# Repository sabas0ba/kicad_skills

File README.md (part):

#  kicad_skills — a containerised circuit-design toolkit

`eda` is a command-line toolkit for circuit design work: reading datasheets,
simulating analog circuits with ngspice, reviewing KiCad schematics and PCB
artwork, and producing the fabrication package.

**Everything runs inside a container.** KiCad, ngspice and the Python
dependencies are never installed on the host — the only host requirements are
`docker` and `bash`. The KiCad release is a build argument, so it can be pinned
per project.

It is an ordinary CLI that prints JSON and exits non-zero on errors, so it works
the same from a terminal, a `Makefile`, a CI job, or a coding assistant. The
repository also ships [usage guides](docs/guides/README.md) for each area —
plain Markdown, worth reading on their own, and installable into whatever layout
your assistant expects.

```bash
./bin/eda.sh doctor                                   # builds the image on first use
./bin/eda.sh gate        hardware/ --policy ai-generated --text   # pass or fail, and why
./bin/eda.sh report      hardware/ -o build/report    # everything, on one page
./bin/eda.sh sch review  hardware/ --text
./bin/eda.sh pcb review  hardware/ --text
./bin/eda.sh sim run     sim/filter.cir -o sim/out
./bin/eda.sh datasheet parse docs/datasheets/lm321.pdf -o /tmp/ds
```

## Install

### Into an existing board project, as a submodule

```bash
cd ~/projects/my-board
git submodule add https://github.com/sabas0ba/kicad_skills tools/kicad_skills
./tools/kicad_skills/bin/install-skills.sh
```

That drops a one-line `bin/eda.sh` shim so the `./bin/eda.sh …` commands work
verbatim from your project root and links the [usage guides](docs/guides/README.md)
into the standard layouts discovered by Codex, compatible assistants, and
Claude Code:

```
my-board/
├── bin/eda.sh                                    shim -> tools/kicad_skills/bin/eda.sh
├── .agents/skills/kicad-pcb-review/SKILL.md ->   ../../../tools/kicad_skills/docs/guides/kicad-pcb-review.md
├── .claude/skills/kicad-pcb-review/SKILL.md ->   ../../../tools/kicad_skills/docs/guides/kicad-pcb-review.md
├── hardware/my-board.kicad_pro
└── tools/kicad_skills/                           the submodule
```

Commit `bin/eda.sh` so everyone who clones the project gets it. Upgrading is
`git submodule update --remote` — the symlinks follow, with no re-install.
The generated skill layouts are outside the submodule, so add `.agents/skills/`
and `.claude/skills/` to the parent project's `.gitignore` unless the project
chooses to track those adapters.

| Flag | Effect |
| --- | --- |
| `--no-guides` | just the CLI shim, nothing else |
| `--dest DIR` | another tool's directory (e.g. `--dest .cursor/rules`) |
| `--copy` | vendor the guides instead of symlinking (Windows checkouts) |
| `--force` / `--uninstall` | replace what is already there / reverse the install |

The guides themselves need no install — they are Markdown in
`tools/kicad_skills/docs/guides/`, readable as they are.

Then, from your project root:

```bash
./bin/eda.sh doctor                       # builds the image on first use (~5 min)
./bin/eda.sh report hardware/ -o build/report
```

### Or standalone

No install step is needed to try it — clone and run:

```bash
git clone https://github.com/sabas0ba/kicad_skills && cd kicad_skills
./bin/eda.sh doctor            # {"kicad_cli": "10.0.4", "ngspice": "...", "ok": true}
./bin/eda.sh report ~/projects/my-board/hardware -o /tmp/report
```

`bin/eda.sh` mounts the git repository root that contains the current directory
at `/work`, runs as your uid/gid (no root-owned files), and gives the container
no network. To work on the toolkit itself, see [AGENTS.md](AGENTS.md).

If you drive this clone with Codex, another Agent Skills-compatible assistant,
or Claude Code, `make skills` mirrors the guides into the layouts they discover.
Those directories are generated and git-ignored — the guides live in
[`docs/guides/`](docs/guides/README.md).

## What it does

```mermaid
flowchart LR
    PDF[datasheet PDF] --> DS[eda datasheet]
    DS -->|part values| SIM[eda sim]
    SIM -->|verified circuit| SCH[eda sch review]
    SCH -->|netlist + ERC| PCB[eda pcb review]
    SCH --> GATE[eda gate]
    PCB --> GATE
    GATE -->|pass| FAB[eda pcb fab]
    SCH --> REP[eda report]
    PCB --> REP
    SIM --> REP
    REP --> HTML[report.html + PNG + PDF + GLB]
```

| Area | What it does | One command | Guide |
| --- | --- | --- | --- |
| Datasheets | Text, parameter tables, embedded figures and rendered page images from a PDF | `eda datasheet parse lm321.pdf -o out/` | [guide](docs/guides/datasheet-analysis.md) |
| Simulation | ngspice op/dc/ac/tran/noise, THD, Monte Carlo tolerance analysis, temperature sweeps — with measurements and plots | `eda sim run filter.cir -o out/` | [guide](docs/guides/spice-simulation.md) |
| Schematic review | Components, nets and hierarchy from `.kicad_sch`; ERC plus decoupling / floating-input / annotation / pull-up checks, drawing readability (grid, junctions, overlap, page) and part specification (ratings, derating, part numbers) | `eda sch review hardware/ --text` | [guide](docs/guides/kicad-schematic-review.md) |
| Board review | DRC, schematic parity, track widths, drills, exact board-edge clearance, ground pour, silkscreen over pads, placement grid and rotation, track stubs and acute corners, decoupling vias; current capacity, resistance and impedance from the stackup — closed forms, or a 2D field solve with `--solve`; a steady-state temperature map and heating curve for stated dissipations (`pcb thermal`); near- and far-end crosstalk of the coupled runs from solved line matrices (`pcb crosstalk`); layer plots and 3D renders | `eda pcb review hardware/ --text` | [guide](docs/guides/kicad-pcb-review.md) |
| Design gate | One pass/fail verdict over ERC, DRC and both reviews against a stated policy; readability, layout-practice and part-specification rules; waivers that must carry a reason | `eda gate hardware/ --policy ai-generated` | [guide](docs/guides/kicad-design-gate.md) |
| Fabrication | Gerbers, Excellon drill, pick-and-place, BOM, STEP/IPC-2581, zipped with a manifest | `eda pcb fab hardware/ -o fab/` | [guide](docs/guides/kicad-fabrication-output.md) |
| The container | Build, pin, verify and troubleshoot the toolchain | `eda doctor` | [guide](docs/guides/eda-environment.md) |

### Examples

**Review a board and see why** — findings are structured, so they can be
filtered, counted and gated on in CI; `--text` is the human digest.

```console
$ ./bin/eda.sh pcb review hardware/ --text
## summary: error=1, warning=3, info=4

## findings
  ERROR   board.copper_outside_outline: 46 copper item(s) lie outside the board outline
  WARNING board.edge_clearance: 2 copper item(s) within 0.3 mm of the board outline
  WARNING layout.decoupling_distance [U3.14 / +3V3]: C12 is 8.4 mm away
  INFO    board.size: board outline is 63.5 x 40.6 mm
```

Exit code is `2` when a review found errors, so `eda pcb review hardware/` is
also a CI gate; `-o report.json` keeps the structured version.

**Hold a generated design to a standard** — a review lists what is wrong; a
gate says whether that is acceptable, against a policy the project committed to.

```console
$ ./bin/eda.sh gate hardware/ --policy ai-generated --text
# gate FAIL: hardware/ against policy 'ai-generated'

## after the policy: error=11, warning=0, info=2
  over the limit: 11 error(s), 0 allowed

## blocking
  ERROR   schematic/readability.off_grid_pin: 12 pin(s) are off the 1.27 mm grid -
          wires that meet them look connected and are not (reported as warning)
  ERROR   schematic/spec.voltage_derating [/:C7]: C7 is rated 6.3 V and sits on a 12 V rail
  ERROR   board/silk.over_pad: 4 silkscreen item(s) print across a pad (reported as warning)

## waived
  drc.lib_footprint_mismatch: our footprints are project-local copies
```

None of that is something ERC or DRC has an opinion about, which is exactly why
a design can be ERC-clean, DRC-clean and still be one no engineer would sign.
`(reported as warning)` is the policy at work — and a waiver without a stated
reason is refused, so nothing is passed over quietly.

`eda gate --list-rules` prints the whole contract: every rule, the exact
condition that makes it fire, the threshold that tunes it and its default, and
the policies under which it blocks. It is assembled from the rule modules, and
`tests/test_rule_spec.py` reads their source, so a rule the catalogue does not
describe — or an entry no rule produces — fails the build. See the
[design gate guide](docs/guides/kicad-design-gate.md) for the evaluation rules
and the exit codes.

**Simulate before committing to a part value** — the −3 dB corner, the phase
margin and the tolerance spread come back as numbers, not a picture to squint at.

```console
$ ./bin/eda.sh sim montecarlo sim/rc.cir -o sim/mc \
    --vary R1=1% --vary C1=10% --metric 'ac.v(out).f_minus_3db_hz' --trials 200
{"metric": "ac.v(out).f_minus_3db_hz", "nominal_metric": 997.7,
 "statistics": {"samples": 200, "mean": 1001.1, "stdev": 35.5,
                "p05": 940.1, "median": 1000.7, "p95": 1064.0, "spread_pct": 20.4},
 "sensitivity": {"explained_pct": 99.7, "parameters": [
     {"parameter": "C1", "contribution_pct": 99.3, "elasticity": -0.99},
     {"parameter": "R1", "contribution_pct":  0.7, "elasticity": -0.96}]},
 "failures": [], "histogram": "sim/mc/histogram.png", "csv": "sim/mc/trials.csv"}
```

The 10 % capacitor is the entire spread; the 1 % resistor is noise. That is the
line item worth changing, and it came out of the trials that were already run.

**Read a datasheet without opening a viewer** — page images for the curves,
tables for the numbers.

```console
$ ./bin/eda.sh datasheet find docs/lm321.pdf "supply current"
[{"page": 3, "line": "Supply Current  IS  VS = 5 V, no load  0.43  0.75  mA"}]
$ ./bin/eda.sh datasheet pages docs/lm321.pdf -o out/ --pages 7 --dpi 200
```

**One command for the whole project** — see [the worked example](#worked-example-a-real-board)
below.

```bash
./bin/eda.sh report hardware/ -o build/report --glb
open build/report/report.html
```

## What the gate is worth, in pictures

Five complete designs are generated by [`tools/make_examples.py`](https://github.com/sabas0ba/kicad_skills/blob/main/tools/make_examples.py)
and shipped twice: once as the generator first left them, and once after
`eda gate` had been run and every finding answered. Same circuit, same nets,
same parts — the difference is entirely what the gate had an opinion about.

**A schematic.** The Pico carrier. On the left: an empty title block, not one
note, and eighteen power symbols pointing in four different directions. On the
right: a title that says what the board is, fifteen notes recording why the
values are what they are, and every power symbol upright:

| as generated | after the gate |
| --- | --- |
|  |  |

**A board.** The 12 V → 5 V buck. On the left: no ground pour, not one via,
every track 0.25 mm whatever it carries, and nothing on the silkscreen at all.
On the right: the plane poured on both faces and stitched with 79 vias, power
copper at 1.0 mm and tapered into every land, screw holes that clear an M3
washer, and a regulator tab relieved so a reflow oven can still solder it:

| as generated | after the gate |
| --- | --- |
|  |  |

**And the motor driver**, which went from one track width for the whole board
to fifteen — motor outputs, logic and the charge pump each sized for what they
carry — and gained the plane its H-bridge returns through:

| as generated | after the gate |
| --- | --- |
|  |  |

The scoreboard, under each project's own policy:

| design | as generated | after the gate |
| --- | --- | --- |
| buck-5v | **FAIL** — 45 blocking | **PASS** |
| motor-driver | **FAIL** — 43 blocking | **PASS** |
| pico-carrier | **FAIL** — 50 blocking | **PASS** |
| opamp-filter | **FAIL** — 33 blocking | **PASS** |
| fpga-audio | **FAIL** — 34 blocking | **PASS** |

All five gated boards are clean under KiCad's own DRC on both versions in the
matrix, with nothing unconnected, and every finding that remains is a waiver
carrying the sentence that excuses it.

**[examples/](examples/README.md) is the long version**: all five designs, both
faces of every board, a third column showing what the generator produces *today*
(the reviews went into the generator, not into patches on its output), and
[REVIEW.md](examples/REVIEW.md) — twenty rounds of a reviewer reading the
boards, and what each finding became: a rule, a fix, or a waiver with its
argument.

## Pinning the KiCad version

```bash
KICAD_VERSION=10.0.4 make build     # default, current stable
KICAD_VERSION=9.0.9  make build     # a second image for older projects
KICAD_VERSION=9.0.9 ./bin/eda.sh pcb review board.kicad_pcb
```

Each version produces its own image tag (`eda-toolkit:<version>`) so several can
coexist. Tags: <https://hub.docker.com/r/kicad/kicad/tags>. KiCad upgrades
project files in place when it opens something older than itself, so match the
version to the project.

CI runs the **whole suite against both 10.0.4 and 9.0.9**, because "the KiCad
version is configurable" is a claim that has to be backed up. It is what caught
these, all of which are handled at runtime rather than pinned away:

* `pcb export pdf --scale`, `pcb export gerbers --check-zones`,
  `pcb drc --refill-zones` and `pcb export stats` are KiCad 10 additions. The
  wrapper asks the binary what it supports (`kicad_cli.supports`) instead of
  keeping a version table, so an untested release degrades rather than crashes.
* ngspice never initialises the imaginary half of an AC sweep's frequency
  column. ngspice 44 leaves a denormal there and taking the magnitude looks
  fine; the ngspice 39 that ships with KiCad 9 left `-1.8e199`, and every
  frequency measurement became nonsense. Only the real part is defined.

Adding a version is a digest in `docker/kicad-digests.txt` plus an entry in the
workflow matrix — `tests/test_pinning.py` fails if the two disagree.

## Worked example: a real board

Everything below is actual output from the **Open Air Max** demo project that
ships with KiCad (210 footprints, 4 layers, a 3-sheet hierarchical schematic) —
a far better test of "does this help?" than a two-resistor fixture. One command
produced all of it:

```bash
./bin/eda.sh report openair-max/ -o build/report --dpi 150 --glb
```

```
build/report/
├── report.html          the page below, self-contained
├── report.md            same content, for a PR comment or a commit message
├── report.json          every finding, machine readable
├── bom.csv
├── schematic/           schematic.pdf + one PNG per sheet + contact sheet
└── board/               6 view plots, 4 per-layer plots, 3 renders,
                         contact-sheet.png, board.glb, the PDFs behind them
```

**The board at a glance** — 13 plots and renders tiled into one image, so
"is anything on the wrong layer" is one look, not thirteen file-opens:

**3D, for the things no 2D plot shows** — connector orientation, component
collisions, which side is which. `--glb` additionally writes a `board.glb` that
GitHub and every browser render interactively:

**The schematic**, rasterised per sheet plus a real PDF (sheet 1 of 3):

**And the verdict**, abridged from `report.md` — note the collapsing: 199
identical drill violations are one line, not 199:

```markdown
## Verdict
* schematic: 3 error, 19 warning, 4 info
* board: 8 error, 26 warning, 6 info
* 99.45 x 72.0 mm, 4 layers, 210 footprints, 156 nets, 410 vias

## Board findings
| severity | rule | where | message |
| --- | --- | --- | --- |
| error   | `drc.drill_out_of_range` | 199 locations | 199 occurrences. First: Hole size out of range (min hole 0.5080 mm; actual 0.4000 mm) |
| error   | `drc.clearance`          | 13 locations  | 13 occurrences. First: Clearance violation (clearance 0.1000 mm; actual 0.0910 mm) |
| error   | `drc.zones_intersect`    | Zone [BAT-] on F.Cu, priority 5 | Copper zones intersect (must have distinct priorities) |
| warning | `drc.parity.net_conflict`| Pad 6 of I2C3 on B.Cu | Pad net doesn't match net given by schematic (GND) |
| warning | `drc.silk_edge_clearance`| 8 locations   | 8 occurrences. First: Silkscreen clipped by board edge |
```

### Simulation

The same "show, don't describe" applies to analog work. An AC sweep of the RC
reference circuit, and 200 Monte Carlo trials of the same circuit with 1 %
resistors and 10 % capacitors:

| `sim run` (AC) | `sim montecarlo` |
| --- | --- |
|  |  |

```json
{"nominal_metric": 997.7,
 "statistics": {"samples": 200, "mean": 1001.1, "stdev": 35.5,
                "p05": 940.1, "median": 1000.7, "p95": 1064.0, "spread_pct": 20.4}}
```

The 10 % capacitor sets the spread: ±1 % on the resistor barely moves it. That
is the kind of answer that changes a BOM line.

Provenance and licensing of these images: [`docs/examples/README.md`](docs/examples/README.md).

## Command reference

```
eda doctor                                    tool versions in the environment
eda gate         TARGET [--policy NAME|FILE] [--text] [--threshold KEY=VALUE]
                        [--collapse N] [-o verdict.json]
eda gate         --list-policies | --list-rules [--text]
eda diff         OLD NEW -o DIR [--dpi 150] [--no-images]
eda report       TARGET -o DIR [--dpi 200] [--glb] [--simulation NETLIST]
                              [--no-3d] [--no-per-layer] [--no-bom] [--title T]

eda datasheet info   PDF
eda datasheet find   PDF QUERY... [--regex]
eda datasheet text   PDF [--pages 1-5] [--layout] [--ocr]
eda datasheet tables PDF [--pages 5]
eda datasheet images PDF -o DIR [--pages]
eda datasheet pages  PDF -o DIR [--pages] [--dpi 200]
eda datasheet parse  PDF -o DIR [--renders] [--ocr]

eda sim lint     NETLIST
eda sim run      NETLIST -o DIR [--no-plots] [--timeout S]
eda sim montecarlo NETLIST -o DIR --vary R1=1% --metric ac.v(out).f_minus_3db_hz [--trials N]
eda sim temperature NETLIST -o DIR [--temperatures -40 25 85] [--metric ...]
eda sim measure  RAW [--thd SIGNAL --fundamental HZ] [--skip S]
eda sim plot     RAW -o DIR [--signals ...]
eda sim netlist  SCHEMATIC -o FILE           export a SPICE deck from KiCad

eda sch info     TARGET [--no-cli]
eda sch review   TARGET [--text] [--collapse N] [--threshold KEY=VALUE] [-o report.json] [--no-cli]
eda sch bom      TARGET -o bom.csv [--group-by ...] [--fields ...]
eda sch erc      TARGET                      raw KiCad ERC JSON
eda sch netlist  TARGET [--format json|kicadxml|spice|...] [-o FILE]
eda sch render   TARGET -o DIR [--dpi 200]   PDF + one PNG per sheet + contact sheet
eda sch pdf      TARGET -o FILE              just the PDF

eda pcb info     TARGET
eda pcb review   TARGET [--text] [--collapse N] [--threshold KEY=VALUE] [-o report.json]
eda pcb fab      TARGET -o DIR [--step] [--ipc2581] [--pos-format csv]
                              [--preview] [--background white|black|transparent]
eda pcb drc      TARGET [--no-parity]        raw KiCad DRC JSON
eda pcb render   TARGET -o DIR [--views ...] [--per-layer] [--no-3d] [--no-sheet]
                              [--glb] [--dpi 300]
                              [--background white|black|transparent]
eda pcb glb      TARGET -o FILE              3D model a browser can display
eda pcb electrical TARGET [--temperature-rise K] [--top N] [--solve]
eda pcb crosstalk TARGET [--rise-ns NS] [--swing V] [--min-coupled MM] [--limit N]
                              [-o DIR]
eda pcb thermal  TARGET --power REF=W [--power ...] [--ambient C] [--htc W_M2K]
                              [--step MM] [--transient S] [-o DIR]
eda pcb stats    TARGET
```

`TARGET` accepts a `.kicad_sch`/`.kicad_pcb` file, a `.kicad_pro`, or a project
directory. All commands print JSON by default (the review commands also take
`--text` for a human readable digest) and exit `2` when a review found errors.

### Environment variables

| Variable | Effect |
| --- | --- |
| `KICAD_VERSION` | KiCad release / image tag to use (default `10.0.4`) |
| `EDA_IMAGE` | override the image name entirely |
| `EDA_NETWORK` | `1` gives the container network access (default: offline) |
| `EDA_MOUNT` | host directory to mount at `/work` (default: git root or `$PWD`) |
| `EDA_ENV_PASSTHROUGH` | extra environment variable names to forward |
| `EDA_DOCKER_ARGS` | extra arguments for `docker run` |

## Using it in CI

The reviews are exit-code gates, so a board can be checked on every push the way
code is. In a project that added this as a submodule:

```yaml
# .github/workflows/hardware.yml
- uses: actions/checkout@... # with: submodules: true
- name: Gate the design
  run: ./bin/eda.sh gate hardware/ --policy hardware/gate.toml --text
- name: Review the board
  if: always()
  run: |
    ./bin/eda.sh sch review hardware/ --text
    ./bin/eda.sh pcb review hardware/ --text
- name: Build the report
  if: always()
  run: ./bin/eda.sh report hardware/ -o build/report
- uses: actions/upload-artifact@...
  if: always()
  with: { name: hardware-report, path: build/report }
```

On a pull request the more useful question is what changed. `eda diff` answers it
against the design rather than the file: a moved component rewrites thousands of
coordinates in the `.kicad_pcb`, and a text diff cannot tell that apart from a
rerouted net.

```yaml
- name: What changed
  run: |
    git worktree add /tmp/base "$GITHUB_BASE_REF"
    ./bin/eda.sh diff /tmp/base/hardware hardware/ -o build/diff
    cat build/diff/diff.md >> "$GITHUB_STEP_SUMMARY"
```

```markdown
## Connectivity
* **VCC**: gained U3.14, lost -
## Components
* **R7**: value '10k' -> '4k7'
## Board
* moved: U3 (5.0 mm), C12 (1.2 mm)
## Artwork
* `copper-front`: 0.28% of pixels changed
```

Both drawings are rendered and compared too — the schematic sheets and the board
plots. What only the old revision had is drawn in **red**, what only the new one
has in **green**, over a faded copy of the new drawing, so a part that moved reads
as red where it was and green where it is now. Where the change is a speck on an
A4 sheet, a zoomed crop is written alongside the full page:

| schematic: C2 moved, R1 re-valued | board: the same R1 move |
| --- | --- |
|  |  |

Exit `0` clean, `1` on a usage error, `2` when a review found errors. Loosen or
tighten what counts as an error with `--threshold KEY=VALUE`, or post-process
`report.json` if you want your own policy. This repository's own CI reviews its test
fixture and uploads the report the same way — see
[`ci.yml`](https://github.com/sabas0ba/kicad_skills/blob/main/.github/workflows/ci.yml).

Nothing needs the network at run time, so the container stays offline unless you
ask for `EDA_NETWORK=1`.

## Using it with a coding assistant

The toolkit is a CLI: any assistant that can run a shell command can drive it,
and the JSON output is meant to be parsed rather than screen-scraped. What makes
the difference in practice is not the commands but knowing how to *use* them —
which is what [`docs/guides/`](docs/guides/README.md) is for. Those guides cover
the review methodology, what each finding means, and what the tool cannot judge
for you.

* **Codex and Agent Skills-compatible assistants** discover
  `.agents/skills/<name>/SKILL.md`.
* **Claude Code** discovers `.claude/skills/<name>/SKILL.md`.
* `bin/install-skills.sh` creates both layouts as symlinks by default. Run it in
  this checkout or in a project that uses the submodule. This checkout ignores
  the generated adapters; a parent project must ignore or track its own copies.
* **A tool with another layout** — use
  `./bin/install-skills.sh --dest .cursor/rules --copy`; specifying `--dest`
  installs only that layout.
* **Anything that reads a repository** can instead read `docs/guides/` or
  [`AGENTS.md`](AGENTS.md), which names the guides.
* **No assistant at all** — they are ordinary Markdown, written to be read.

Contributor and agent instructions for this repository itself live in
[`AGENTS.md`](AGENTS.md) (`CLAUDE.md` is a pointer to it, not a second copy).

`eda gate` is the other half of that story. An assistant that generates a
design will read a page of warnings and move on unless something says which of
them were allowed to survive; the gate is that statement, and its exit code is
the loop condition. The [design gate guide](docs/guides/kicad-design-gate.md)
describes the generate → gate → fix loop.

`eda report` exists largely for this use case: an assistant working headlessly
can produce one page — renders, findings, BOM, simulation plots — that a human
can check at a glance instead of taking a summary on trust.

## How it fits together

```
bin/eda.sh            host wrapper: docker run, uid mapping, network policy, path rewriting
bin/install-skills.sh CLI shim + renders docs/guides/ into an assistant's layout
docker/Dockerfile     kicad/kicad:<version> + ngspice + an isolated virtualenv
src/eda_toolkit/
├── cli.py                 the `eda` command
├── gate.py                policies, waivers, and the one pass/fail verdict
├── report.py              the one-command report: collect, then render md/html
├── datasheet/             PDF text, table, image and page extraction
├── spice/                 ngspice runner, raw-file parser, measurements, plots
└── kicad/                 s-expression parser, schematic/board models,
                           outline geometry, kicad-cli wrapper, review rules,
                           renderers, fabrication package
tests/                     pytest suite + fixtures + smoke test
docs/guides/               the usage guides - prose, and the source of truth
docs/examples/             committed output, so the README shows rather than tells
AGENTS.md                  contributor / agent instructions (CLAUDE.md points here)
```

Design notes:

* **KiCad is the source of truth** where it can be: ERC, DRC, netlist export
  and plotting all go through `kicad-cli`. The hand-written parsers add what
  the CLI does not expose (geometry, stackup, pad positions, properties) and
  provide a pure-python fallback so the library, and the test-suite, still work
  without KiCad installed.
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
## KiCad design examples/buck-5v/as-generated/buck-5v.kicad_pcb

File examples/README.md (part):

# Worked examples

Each project here exists twice, generated from one description by
[`tools/make_examples.py`](https://github.com/sabas0ba/kicad_skills/blob/main/tools/make_examples.py):

| | what it is |
| --- | --- |
| `as-generated/` | a deterministic negative control: deliberately incomplete title/part metadata and unreviewed layout details |
| `reviewed/` | the rebuilt baseline accepted by its gate and project-specific contracts, with documented exceptions |

A repository full of good designs proves only that good designs pass. The *pair*
is the evidence: that the rules catch what they claim to catch, and that fixing
what they report converges.

**Gate acceptance is not production sign-off.** These are worked examples,
not hardware-validated reference designs. In particular, the FPGA still has
decoupling-distance exceptions; signal return paths, application-specific
power/thermal budgets and EMC remain engineering review and measurement work.

```bash
./bin/eda.sh gate examples/buck-5v/reviewed     --policy examples/buck-5v/gate.toml --text
./bin/eda.sh gate examples/buck-5v/as-generated --policy examples/buck-5v/gate.toml --text
```

Regenerate the projects with:

```bash
docker run --rm -u $(id -u):$(id -g) -v "$PWD:/work" -w /work \
  -e PYTHONPATH=/work/src -e HOME=/tmp/eda-home \
  --entrypoint python3 eda-toolkit:9.0.9 tools/make_examples.py examples/
```

and the images below with
[`tools/example_images.py`](https://github.com/sabas0ba/kicad_skills/blob/main/tools/example_images.py),
which runs the same two renders for every variant and writes them as JPEG:

```bash
docker run --rm -u $(id -u):$(id -g) -v "$PWD:/work" -w /work \
  -e PYTHONPATH=/work/src -e HOME=/tmp/eda-home \
  --entrypoint python3 eda-toolkit:9.0.9 tools/example_images.py examples/
```

The generator reads KiCad's own symbol and footprint libraries, so these are the
real parts, not simplified copies — which is why it runs inside the container.

After the five were built, the whole set was read the way an engineer would
read it — circuit theory, layout physics, readability — and every finding was
either turned into a rule, fixed in `reviewed/`, or answered with a reasoned
waiver in the project's `gate.toml`. That pass, with what each finding became,
is [REVIEW.md](REVIEW.md).

### Three columns, not two

Each comparison below has three, and the leftmost is the honest one.

| column | what it is |
| --- | --- |
| **first edition** | the board as it came out of the generator the day it was written, before any finding had been read. Recovered from this repository's own history — one `git show` per file, no editing — and rendered with today's renderer so the only difference is the design |
| **as-generated** | what the generator produces *now* when told to skip the review. It is much better than the first edition, because twenty rounds of findings were built into the generator itself rather than patched into the output |
| **reviewed** | the same design with the review applied: what passes `eda gate` |

The middle column is the part that is easy to miss. A tool that only fixed its
own output would leave the first column and the second identical; the distance
between them is the review turned into code, and it arrives before anyone runs
the gate. The distance between the second and the third is what the gate still
had to catch on the day.

The first editions are `ea93330` (buck-5v), `e7ad2d7` (motor-driver),
`b4d66f2` (pico-carrier), `3f796a7` (opamp-filter) and `aee7401` (fpga-audio).

CI requires all five `reviewed/` projects to pass and every `as-generated/`
negative control to fail for its intended missing-title and part-specification
defects. It checks that neither the schematic nor board stage was skipped.
The uploaded JSON verdicts and KiCad reports, not stale finding counts in this
historical walkthrough, are the authority for each revision.

What each of them still carries is a waiver, and a waiver here is a decision
with the argument attached rather than a finding hidden. Package escape necks,
board-only decoupling heuristics and deliberately exposed module rails remain
visible there.

**All five are two-layer boards, and that is a requirement rather than an
outcome.** Layer count is the one board parameter that changes the price of a
prototype run outright, so a design that will not close on two layers grows a
few millimetres of FR4 before it grows a stack. The motor driver pays for that
with one waiver — `route.return_path`, measured at 12.3 mm against a 10 mm
limit, on one logic lane crossing under the bridge outputs — and the
waiver says what a faster design should do instead. CI checks the two-layer
stack and that the ground pour on B.Cu is still mostly one piece.

Two rules keep the rest of it honest. `layout.pour_edge_cut` reports copper
that eats through the outermost millimetre of the ground pour: the rim is what
the board radiates into and what every edge-hugging track returns through, and
a mounting hole may interrupt it where a route may not. `route.under_package`
and `route.via_under_package` keep other nets' tracks and vias out from under
the integrated circuits and connectors, where nothing can be probed, inspected
or reworked once the part is down. All three are warnings that the
`ai-generated` policy blocks on: a shipped board may carry them and be right,
a generated one has no argument for them.

All five carry what a board needs to be *made* as well as to work: the ground
pour is filled by KiCad's own filler against the board's own rules, every
through-hole land is relieved thermally, every track fillets into the land it
enters, and each board has its M3 mounting holes and three fiducials for the
assembly machine to align to. The holes clear the *screw* rather than the
hole - a pan head on a washer is seven millimetres across, and a screw
terminal's wires want two more - which is why the count varies: four where the
board has four free quarters, two on the boards whose left edge is a connector
and a row of resistors. Three that hold a board flat beat four that hold one
side of it. Rounds seventeen and eighteen in [REVIEW.md](REVIEW.md) are where
that came from, and what it cost.

## When these were made, and by what

Both variants carry it in their title block, in the comment fields, on the
schematic and on the board:

```
(comment 1 "generated 2026-09-05 by Claude Code")
(comment 2 "from tools/make_examples.py in sabas0ba/kicad_skills")
```

It matters most on `as-generated`. That variant is a record of what a generator
of this vintage actually produced, and the point of keeping it is to be able to
say later how much has changed — which needs a date on it. The stamp is frozen
in `GENERATED_ON` / `GENERATED_BY` at the top of the generator rather than read
from the clock, so regenerating an unchanged design still produces an unchanged
file; bump them when you regenerate, or pass `--generated-on` / `--generated-by`.

The design's own `title`, `date`, `rev` and `company` are a separate thing and
stay empty on `as-generated` — a generator that leaves them blank is one of the
findings, and the stamp deliberately does not paper over it.

## buck-5v — 12 V to 5 V at 2 A

LM2596S-5, catch diode, output inductor, screw terminals in and out, and a fuse
and a TVS between the input terminal and everything else.

Under KiCad's own ERC and DRC, and the `ai-generated` policy:

| | verdict | schematic (e/w/i) | board (e/w/i) |
| --- | --- | --- | --- |
| `reviewed` | **PASS**, 1 finding waived | 0 / 0 / 0 | 0 / 0 / 5 |
| `as-generated` | **FAIL**, blockers retained | — | — |
| first edition | **FAIL**, 45 blocking | — | — |

### The three, side by side

Everything below is this repository's own output — `eda sch render` and
`eda pcb render`, run on the three variants and cropped. Nothing is drawn by hand.

**The schematic.** Left is the first edition; middle is what the generator
leaves today; right is after the loop. The
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
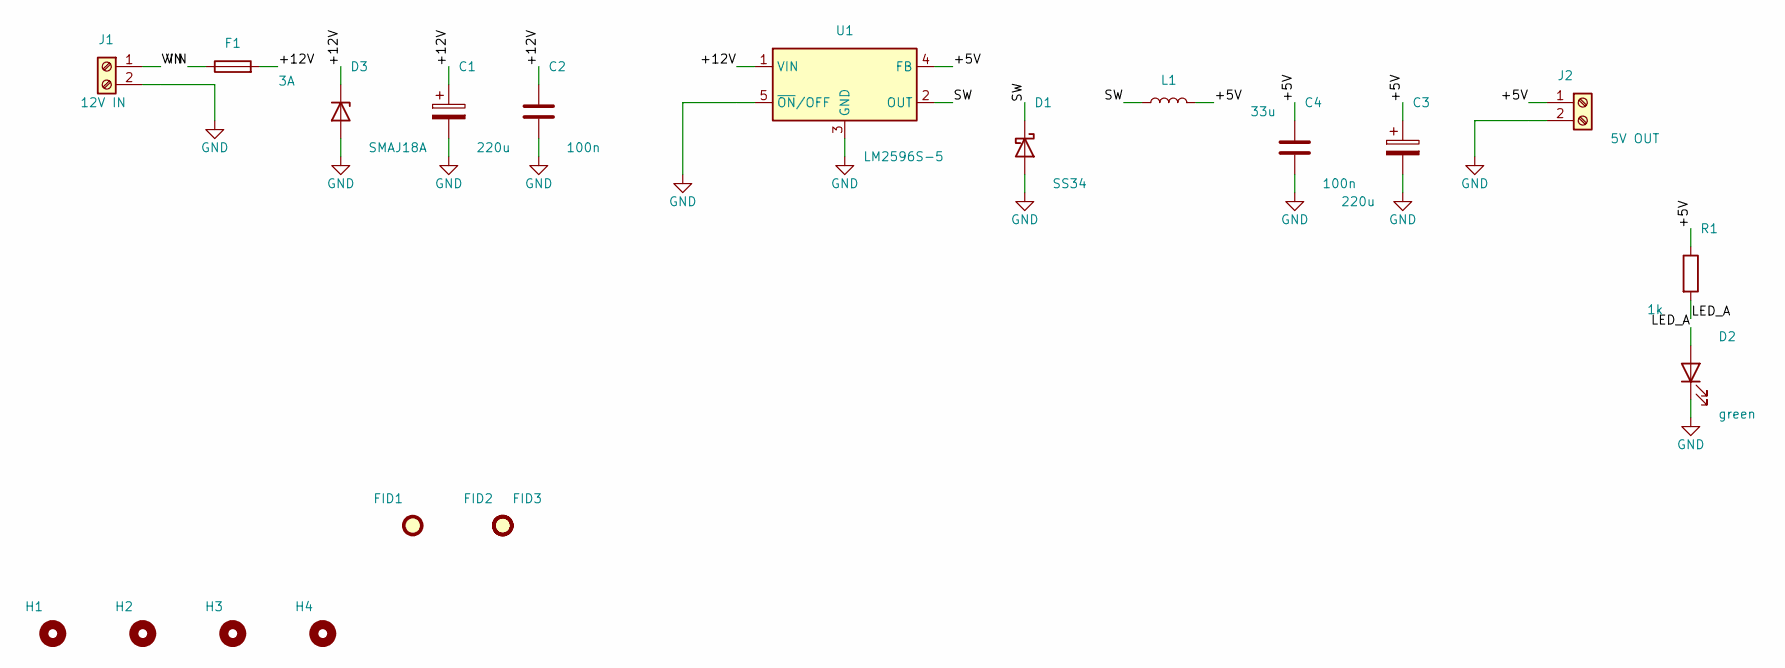
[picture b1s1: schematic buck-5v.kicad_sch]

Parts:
C1, C3: 220u; CP_Elec_8x10.5
C2, C4: 100n; C_0805_2012Metric
D1: SS34; D_SMA
D2: green; LED_0805_2012Metric
D3: SMAJ18A; D_SMA
F1: 3A; Fuse_1206_3216Metric
FID1, FID2, FID3: Fiducial; Fiducial_1mm_Mask2mm
H1, H2, H3, H4: M3; MountingHole_3.2mm_M3
J1: 12V IN; TerminalBlock_Phoenix_MKDS-1,5-2_1x02_P5.00mm_Horizontal
J2: 5V OUT; TerminalBlock_Phoenix_MKDS-1,5-2_1x02_P5.00mm_Horizontal
L1: 33u; L_12x12mm_H8mm
R1: 1k; R_0805_2012Metric
U1: LM2596S-5; TO-263-5_TabPin3

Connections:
/+5V: C3.1, C4.1, J2.1, L1.2, R1.1, U1.4 (FB)
/+12V: C1.1, C2.1, D3.1 (K), F1.2, U1.1 (VIN)
/LED_A: D2.2 (A), R1.2
/SW: D1.1 (K), L1.1, U1.2 (OUT)
/VIN: F1.1, J1.1
GND: C1.2, C2.2, C3.2, C4.2, D1.2 (A), D2.1 (K), D3.2 (A), J1.2, J2.2, U1.3 (GND), U1.5 (~ON/OFF)

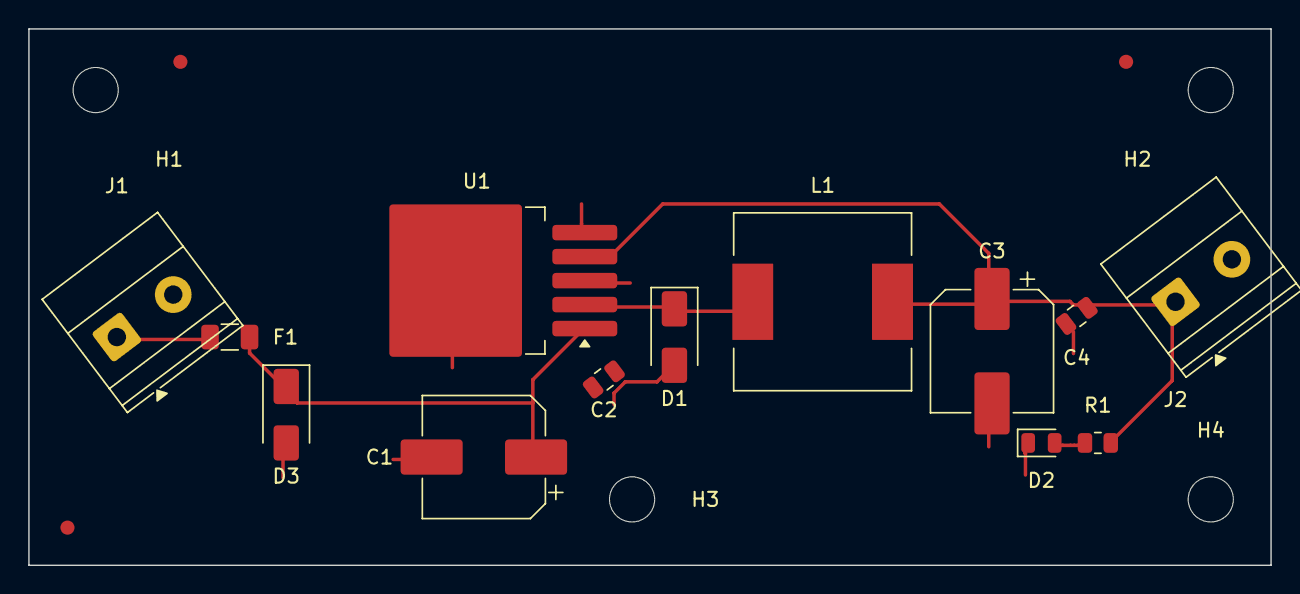
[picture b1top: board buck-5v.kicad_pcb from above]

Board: 2 copper layers, 88.0 x 38.0 mm, 20 parts (0 on the bottom side), 6 nets.

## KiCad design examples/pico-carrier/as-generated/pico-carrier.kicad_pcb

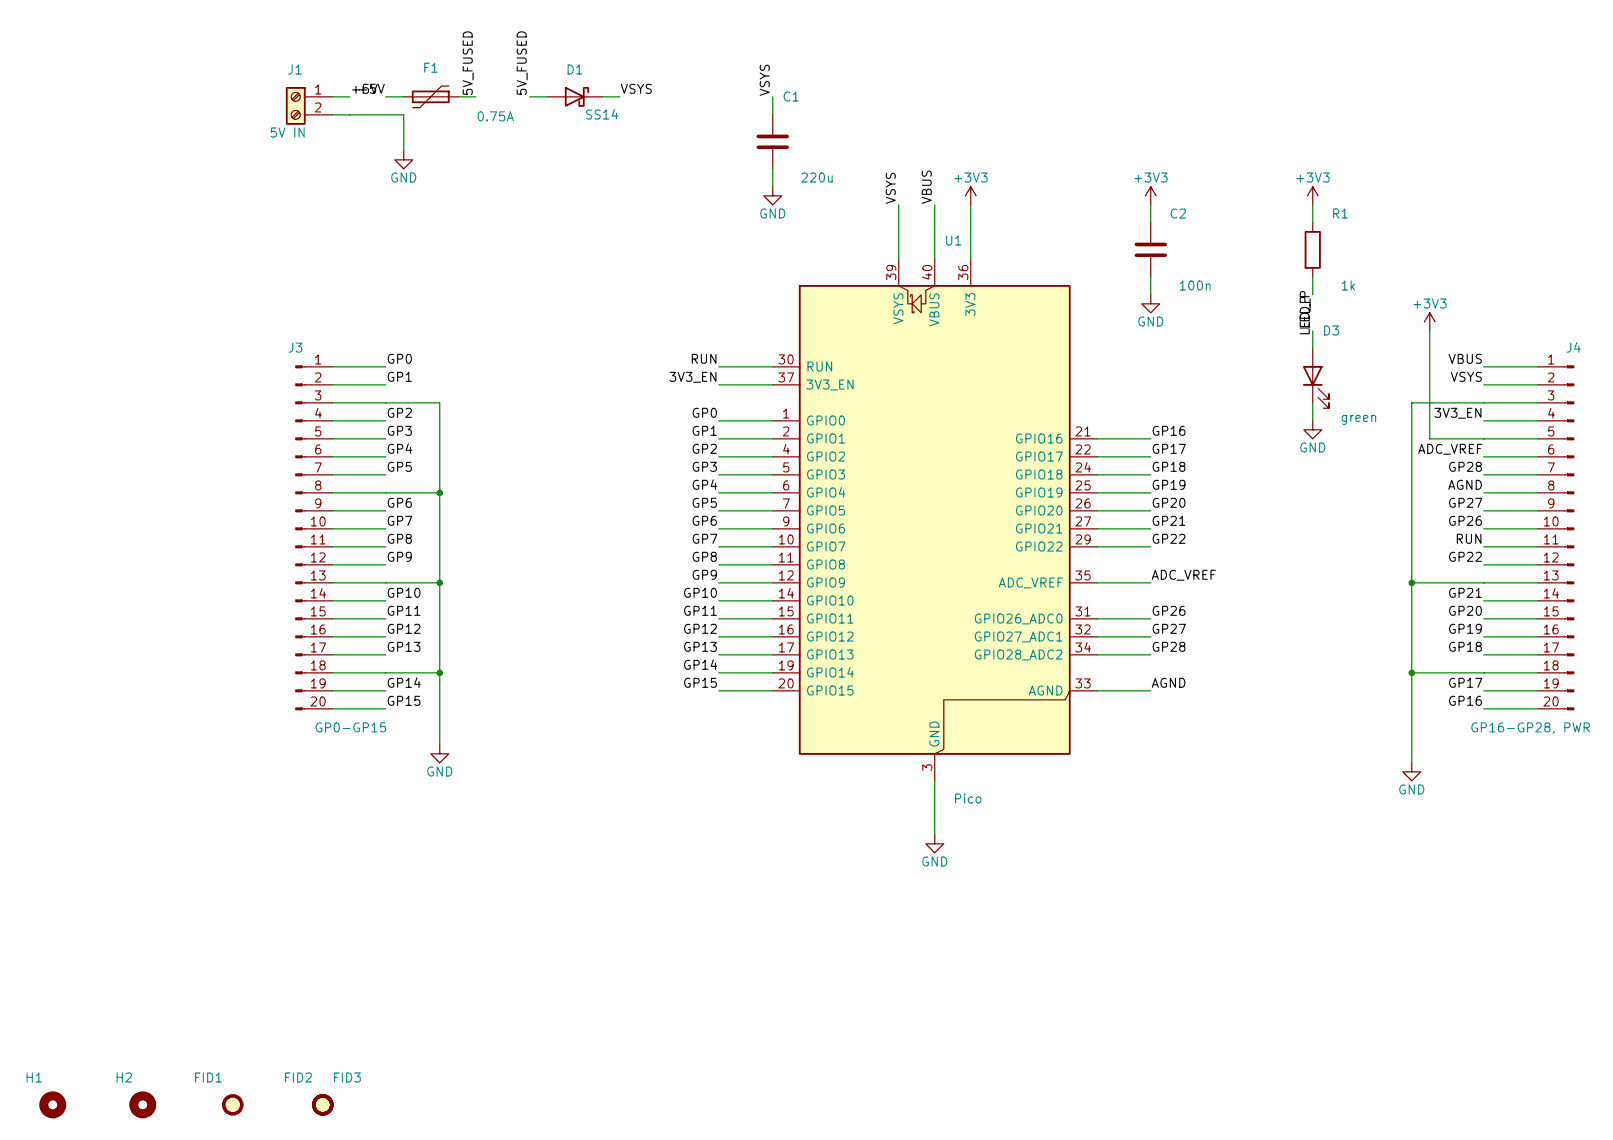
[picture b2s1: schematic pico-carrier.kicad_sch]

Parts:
C1: 220u; C_1210_3225Metric
C2: 100n; C_0805_2012Metric
D1: SS14; D_SMA
D3: green; LED_0805_2012Metric
F1: 0.75A; Fuse_1812_4532Metric
FID1, FID2, FID3: Fiducial; Fiducial_1mm_Mask2mm
H1, H2: M3; MountingHole_3.2mm_M3
J1: 5V IN; TerminalBlock_Phoenix_MKDS-1,5-2_1x02_P5.00mm_Horizontal
J3: GP0-GP15; PinHeader_1x20_P2.54mm_Vertical
J4: GP16-GP28, PWR; PinHeader_1x20_P2.54mm_Vertical
R1: 1k; R_0805_2012Metric
U1: Pico; RaspberryPi_Pico_SMD

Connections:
+3V3: C2.1, J4.5, R1.1, U1.36 (3V3)
/3V3_EN: J4.4, U1.37 (3V3_EN)
/5V_FUSED: D1.2 (A), F1.1
/+5V: F1.2, J1.1
/ADC_VREF: J4.6, U1.35 (ADC_VREF)
/AGND: J4.8, U1.33 (AGND)
/GP0: J3.1, U1.1 (GPIO0)
/GP1: J3.2, U1.2 (GPIO1)
/GP2: J3.4, U1.4 (GPIO2)
/GP3: J3.5, U1.5 (GPIO3)
/GP4: J3.6, U1.6 (GPIO4)
/GP5: J3.7, U1.7 (GPIO5)
/GP6: J3.9, U1.9 (GPIO6)
/GP7: J3.10, U1.10 (GPIO7)
/GP8: J3.11, U1.11 (GPIO8)
/GP9: J3.12, U1.12 (GPIO9)
/GP10: J3.14, U1.14 (GPIO10)
/GP11: J3.15, U1.15 (GPIO11)
/GP12: J3.16, U1.16 (GPIO12)
/GP13: J3.17, U1.17 (GPIO13)
/GP14: J3.19, U1.19 (GPIO14)
/GP15: J3.20, U1.20 (GPIO15)
/GP16: J4.20, U1.21 (GPIO16)
/GP17: J4.19, U1.22 (GPIO17)
/GP18: J4.17, U1.24 (GPIO18)
/GP19: J4.16, U1.25 (GPIO19)
/GP20: J4.15, U1.26 (GPIO20)
/GP21: J4.14, U1.27 (GPIO21)
/GP22: J4.12, U1.29 (GPIO22)
/GP26: J4.10, U1.31 (GPIO26_ADC0)
/GP27: J4.9, U1.32 (GPIO27_ADC1)
/GP28: J4.7, U1.34 (GPIO28_ADC2)
/LED_P: D3.2 (A), R1.2
/RUN: J4.11, U1.30 (RUN)
/VBUS: J4.1, U1.40 (VBUS)
/VSYS: C1.1, D1.1 (K), J4.2, U1.39 (VSYS)
GND: C1.2, C2.2, D3.1 (K), J1.2, J3.3, J3.8, J3.13, J3.18, J4.3, J4.13, J4.18, U1.3 (GND), U1.8 (GND), U1.13 (GND), U1.18 (GND), U1.23 (GND), U1.28 (GND), U1.38 (GND)

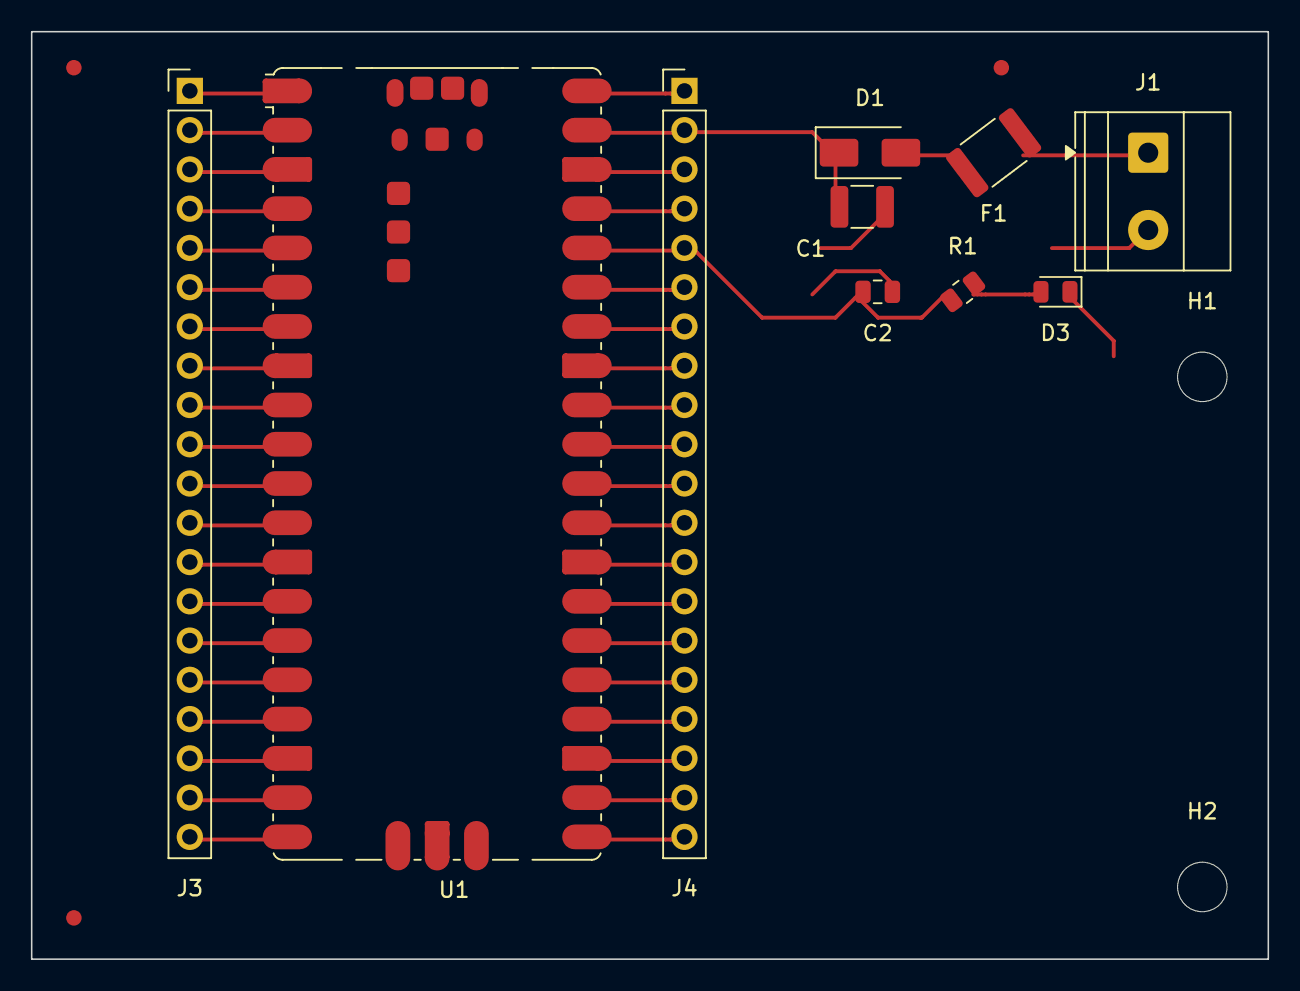
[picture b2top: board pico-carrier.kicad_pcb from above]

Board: 2 copper layers, 80.0 x 60.0 mm, 15 parts (0 on the bottom side), 37 nets.

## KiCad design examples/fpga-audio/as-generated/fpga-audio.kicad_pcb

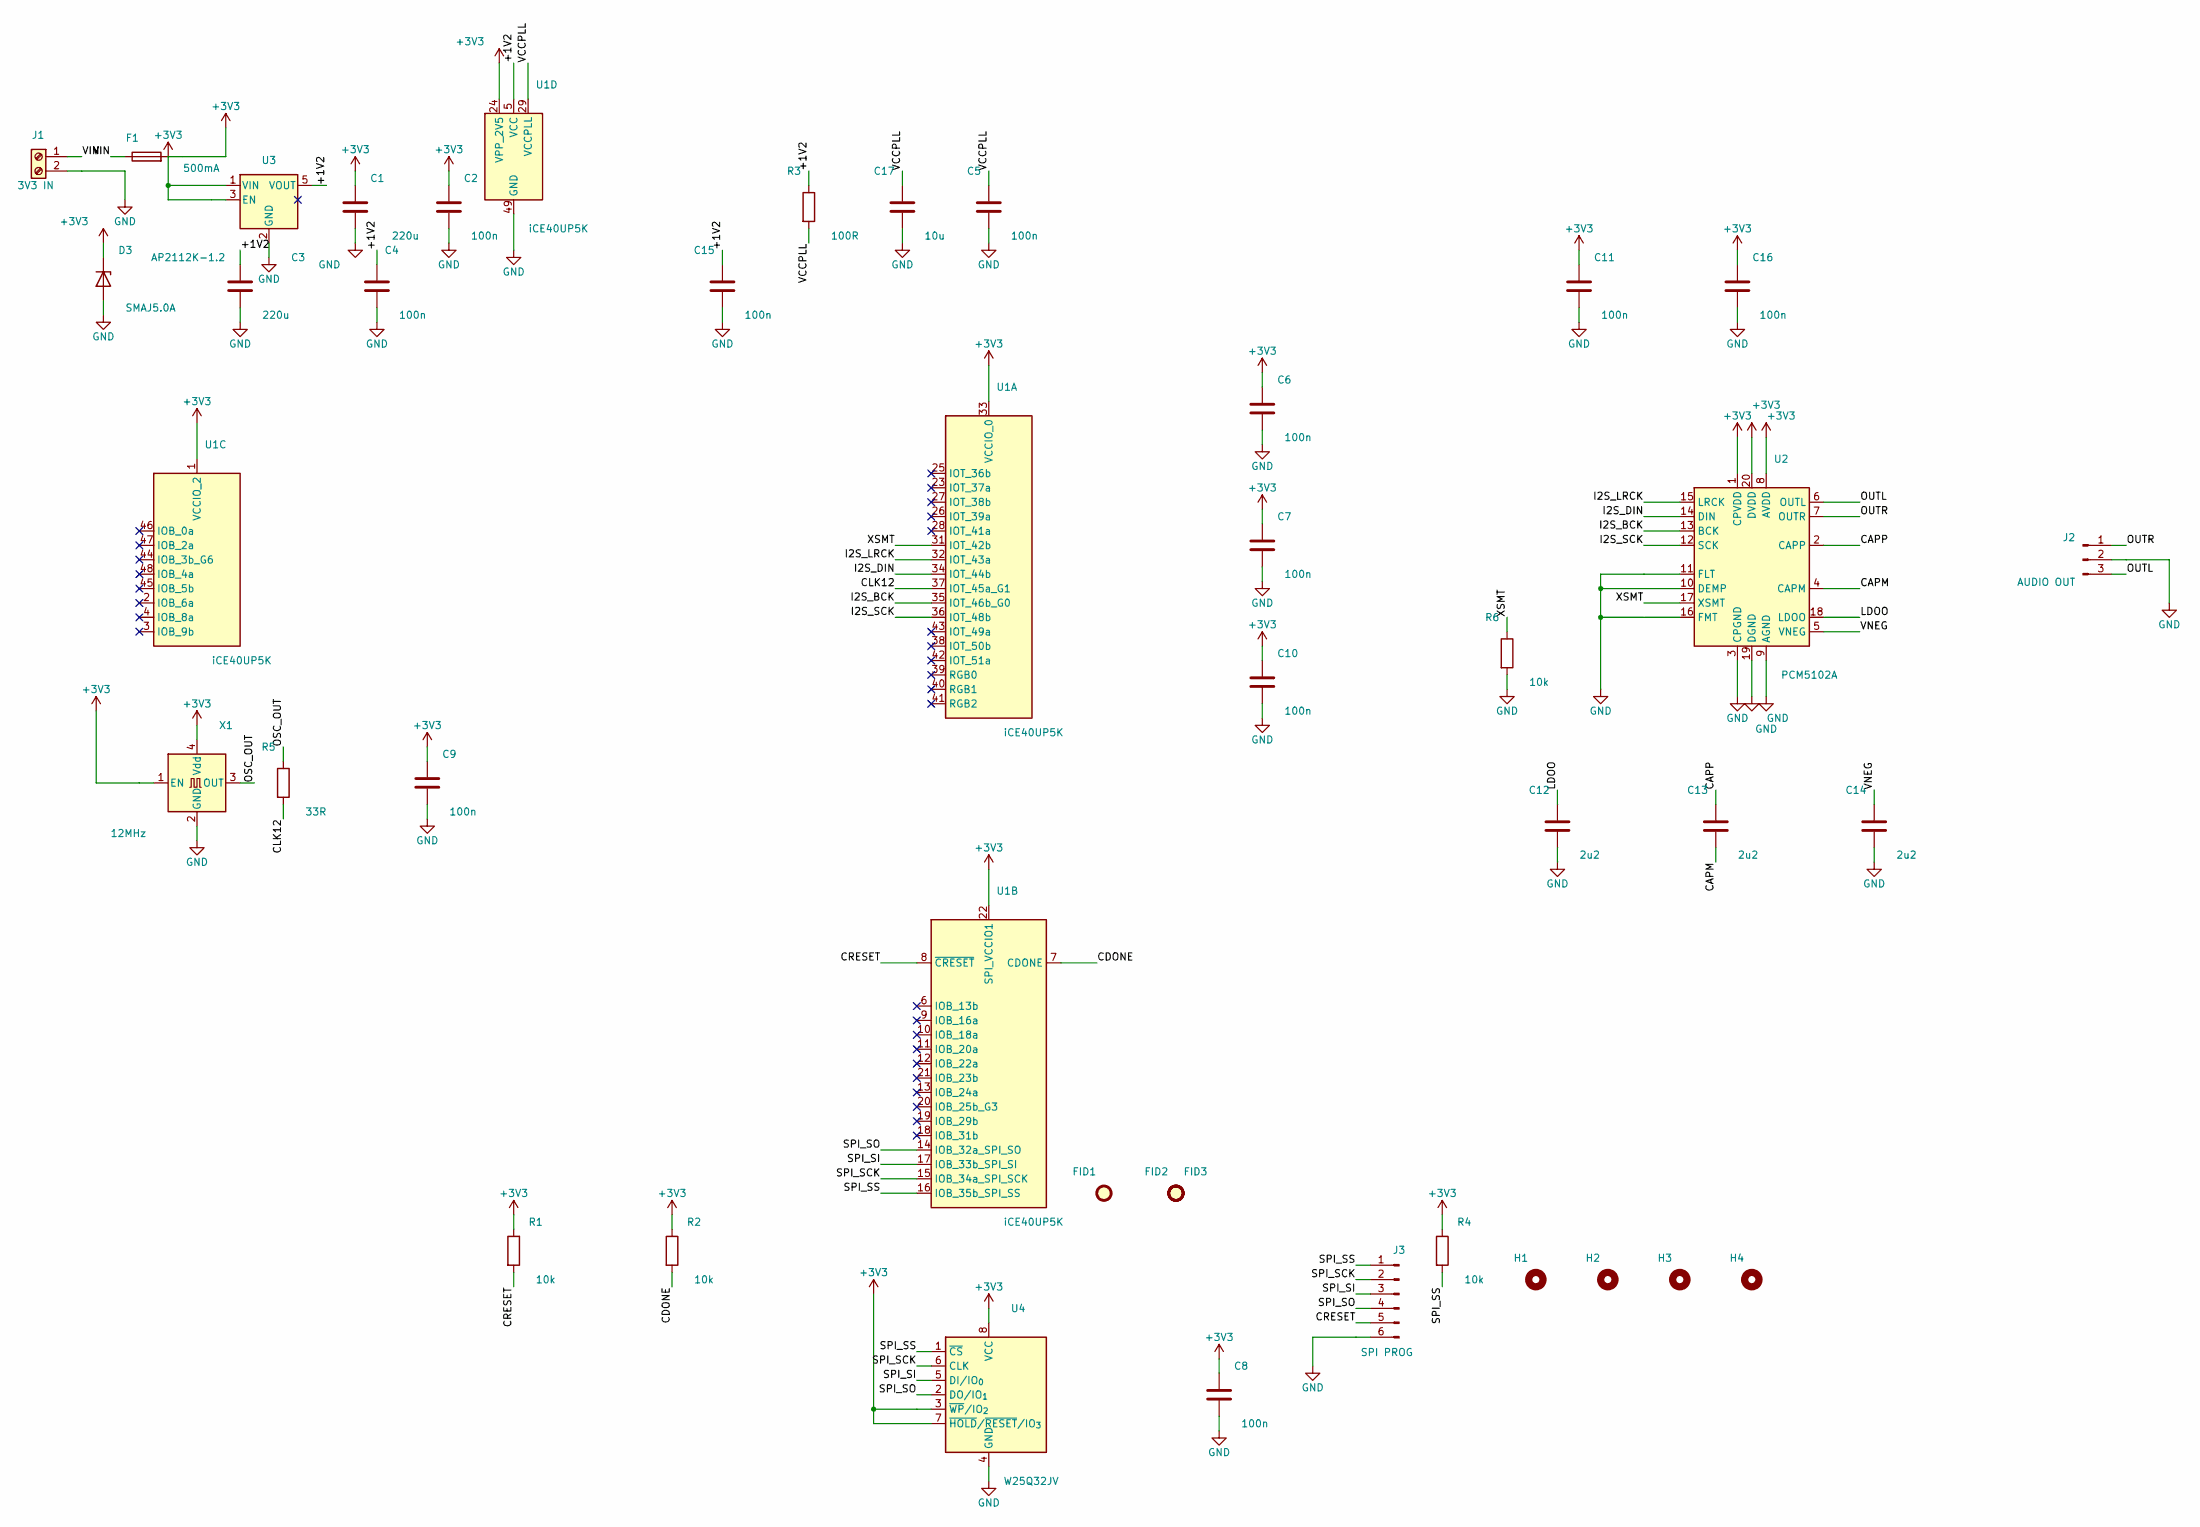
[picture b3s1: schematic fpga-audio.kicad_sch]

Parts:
C1, C3: 220u; C_0603_1608Metric
C2, C4, C5, C6, C7, C8, C9, C10, C11, C15, C16: 100n; C_0603_1608Metric
C12, C13, C14: 2u2; C_0603_1608Metric
C17: 10u; C_0603_1608Metric
D3: SMAJ5.0A; D_SMA
F1: 500mA; Fuse_1206_3216Metric
FID1, FID2, FID3: Fiducial; Fiducial_1mm_Mask2mm
H1, H2, H3, H4: M3; MountingHole_3.2mm_M3
J1: 3V3 IN; TerminalBlock_Phoenix_MKDS-1,5-2_1x02_P5.00mm_Horizontal
J2: AUDIO OUT; PinHeader_1x03_P2.54mm_Vertical
J3: SPI PROG; PinHeader_1x06_P2.54mm_Vertical
R1, R2, R4, R6: 10k; R_0603_1608Metric
R3: 100R; R_0603_1608Metric
R5: 33R; R_0603_1608Metric
U1: iCE40UP5K; QFN-48-1EP_7x7mm_P0.5mm_EP3.5x3.5mm
U2: PCM5102A; TSSOP-20_4.4x6.5mm_P0.65mm
U3: AP2112K-1.2; SOT-23-5
U4: W25Q32JV; SOIC-8_3.9x4.9mm_P1.27mm
X1: 12MHz; Oscillator_SMD_Abracon_ASE-4Pin_3.2x2.5mm

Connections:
+3V3: C1.1, C2.1, C6.1, C7.1, C8.1, C9.1, C10.1, C11.1, C16.1, D3.1 (K), F1.2, R1.1, R2.1, R4.1, U1.1 (VCCIO_2), U1.22 (SPI_VCCIO1), U1.24 (VPP_2V5), U1.33 (VCCIO_0), U2.1 (CPVDD), U2.8 (AVDD), U2.20 (DVDD), U3.1 (VIN), U3.3 (EN), U4.3 (~WP/IO_{2}), U4.7 (~HOLD/~RESET/IO_{3}), U4.8 (VCC), X1.1 (EN), X1.4 (Vdd)
/+1V2: C3.1, C4.1, C15.1, R3.1, U1.5 (VCC), U1.30 (VCC), U3.5 (VOUT)
/CAPM: C13.2, U2.4 (CAPM)
/CAPP: C13.1, U2.2 (CAPP)
/CDONE: R2.2, U1.7 (CDONE)
/CLK12: R5.2, U1.37 (IOT_45a_G1)
/CRESET: J3.5, R1.2, U1.8 (~CRESET)
/I2S_BCK: U1.35 (IOT_46b_G0), U2.13 (BCK)
/I2S_DIN: U1.34 (IOT_44b), U2.14 (DIN)
/I2S_LRCK: U1.32 (IOT_43a), U2.15 (LRCK)
/I2S_SCK: U1.36 (IOT_48b), U2.12 (SCK)
/LDOO: C12.1, U2.18 (LDOO)
/OSC_OUT: R5.1, X1.3 (OUT)
/OUTL: J2.3, U2.6 (OUTL)
/OUTR: J2.1, U2.7 (OUTR)
/SPI_SCK: J3.2, U1.15 (IOB_34a_SPI_SCK), U4.6 (CLK)
/SPI_SI: J3.3, U1.17 (IOB_33b_SPI_SI), U4.5 (DI/IO_{0})
/SPI_SO: J3.4, U1.14 (IOB_32a_SPI_SO), U4.2 (DO/IO_{1})
/SPI_SS: J3.1, R4.2, U1.16 (IOB_35b_SPI_SS), U4.1 (~CS)
/VCCPLL: C5.1, C17.1, R3.2, U1.29 (VCCPLL)
/VIN: F1.1, J1.1
/VNEG: C14.1, U2.5 (VNEG)
/XSMT: R6.1, U1.31 (IOT_42b), U2.17 (XSMT)
GND: C1.2, C2.2, C3.2, C4.2, C5.2, C6.2, C7.2, C8.2, C9.2, C10.2, C11.2, C12.2, C14.2, C15.2, C16.2, C17.2, D3.2 (A), J1.2, J2.2, J3.6, R6.2, U1.49 (GND), U2.3 (CPGND), U2.9 (AGND), U2.10 (DEMP), U2.11 (FLT), U2.16 (FMT), U2.19 (DGND), U3.2 (GND), U4.4 (GND), X1.2 (GND)

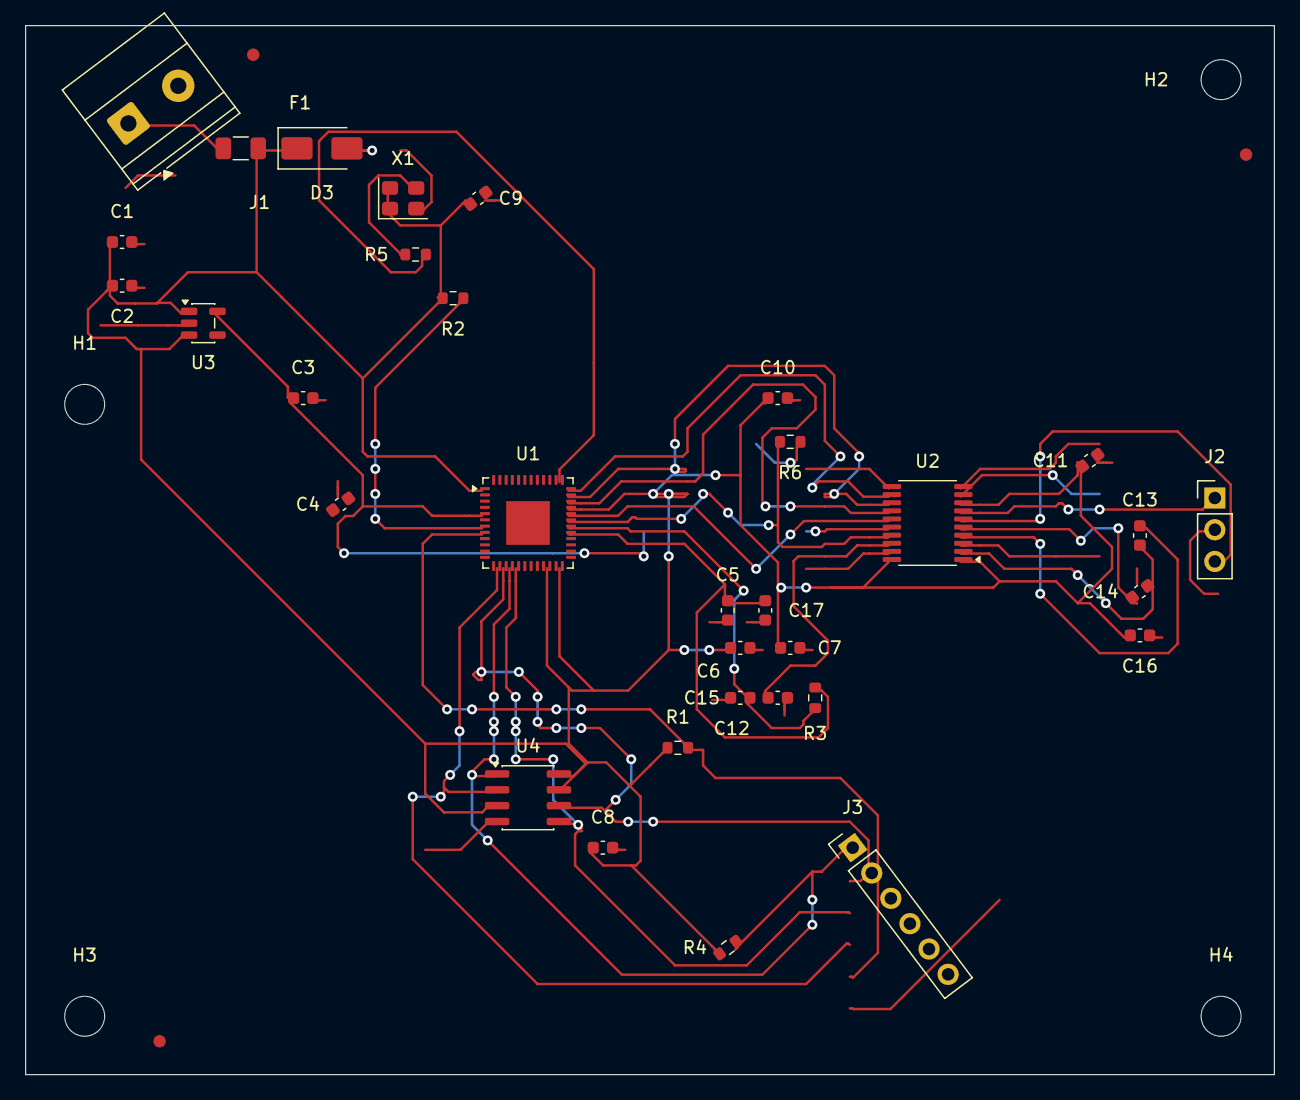
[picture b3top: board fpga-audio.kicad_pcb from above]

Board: 2 copper layers, 100.0 x 84.0 mm, 40 parts (0 on the bottom side), 24 nets.

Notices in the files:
README.md:
License: Apache-2.0
